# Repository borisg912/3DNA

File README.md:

# 3DNA - Interactive DNA Learning Model

**3DNA** is an educational 3D-printed DNA model that combines physical structure with interactive electronics to help students understand DNA base pairing through hands-on learning.

**Website**: [Project showcase and app downloads](Website)

## 🧬 Project Overview

This project creates a flat cylindrical DNA model with:
- **Magnetic DNA bases** with color-coded NeoPixel LEDs and unique resistor values for identification
- **Interactive base pairing game** that validates correct DNA base connections
- **Smart home integration** with multiple connectivity options
- **Companion applications** for Android and Windows

## 📦 Components

### Hardware
- **ESP32-C6** microcontroller on custom PCB (3-3.3V logic)
- **13 DNA bases** (12 helix positions + 1 foundation) with NeoPixels and resistors
- **2x CD74HC4067 multiplexers**: one at 3.3V for resistor voltage divider, one at 5V for NeoPixel control
- **SN74AHCT125N** buffer gate for driving 5V signals from ESP32's 3V
- **TEMT6000** ambient light sensor for dynamic brightness control
- **MPU-6500** gyroscope/inclinometer for spatial orientation
- **DFPlayer Mini** for audio feedback
- **BQ25895** power management IC with USB/USB-C quick charging (up to 9V, 25W@3A)
- **MP8715** voltage regulator (5-9V to 5V)
- **4x 18650 Li-ion batteries** (user-replaceable) with per-cell protection: PPTC fuses + AO3401A + DW01 + FS8205A
- **FQP30N06L** MOSFET for fan control
- **BAT54C** Schottky diode
- **NeoPixel strips** for visual effects (5V)
- **Touch button** for user interaction
- **Backboard button** for system functions

### Software
- **ESP-IDF firmware** for ESP32-C6
- **Android application** for mobile control
- **Windows UWP application** for desktop

## 🎯 Features

### Interactive Learning Mode
- **Base Identification**: Each base has a unique resistor value read via voltage divider
- **Color Coding**: NeoPixels light up in base-specific colors (A, T, C, G)
- **Pair Validation**: Check correct base pairing (A-T, C-G) with visual feedback
- **Error Highlighting**: Wrong bases light up in red for easy identification

### Smart Home Mode
- **Multi-protocol connectivity**: Wi-Fi, Bluetooth/BLE, Zigbee, Thread
- **Remote control**: Control NeoPixels via companion apps
- **Motion sensing**: Gyroscope triggers commands on movement
- **Ambient lighting**: Dynamic brightness based on environment

### Power Management
- **Battery operation**: 2-4 cell configuration
- **USB charging**: With power delivery management
- **Sleep modes**: Low-power states for battery conservation
- **Thermal management**: Fan control based on temperature

## 🛠️ Development Status

- **Hardware**: PCB design in KiCad (v4.1 final)
- **Firmware**: ESP-IDF framework with modular components
- **Mobile**: Android app foundation
- **Desktop**: Windows UWP app starter

## 📁 Project Structure

```
3DNA/
├── Embedded/          KiCad PCB files
├── EmbeddedCode/      ESP32-C6 firmware (ESP-IDF)
├── AppAndroid/        Android mobile app
├── AppWindows/        Windows UWP desktop app
├── Website/           Project showcase website
└── Assets/            Graphics and media
```

## 📄 Documentation

- [English README](README.md)
- [Български README](README.BG.md)

## 🤝 Contributing

This is a school project developed for educational purposes. Contributions and feedback are welcome for improving the learning experience and technical implementation.

## 📜 License

This project is licensed under **GNU GPL v3** - see [LICENSE](LICENSE) for details.

---

*Built with passion for education and technology*

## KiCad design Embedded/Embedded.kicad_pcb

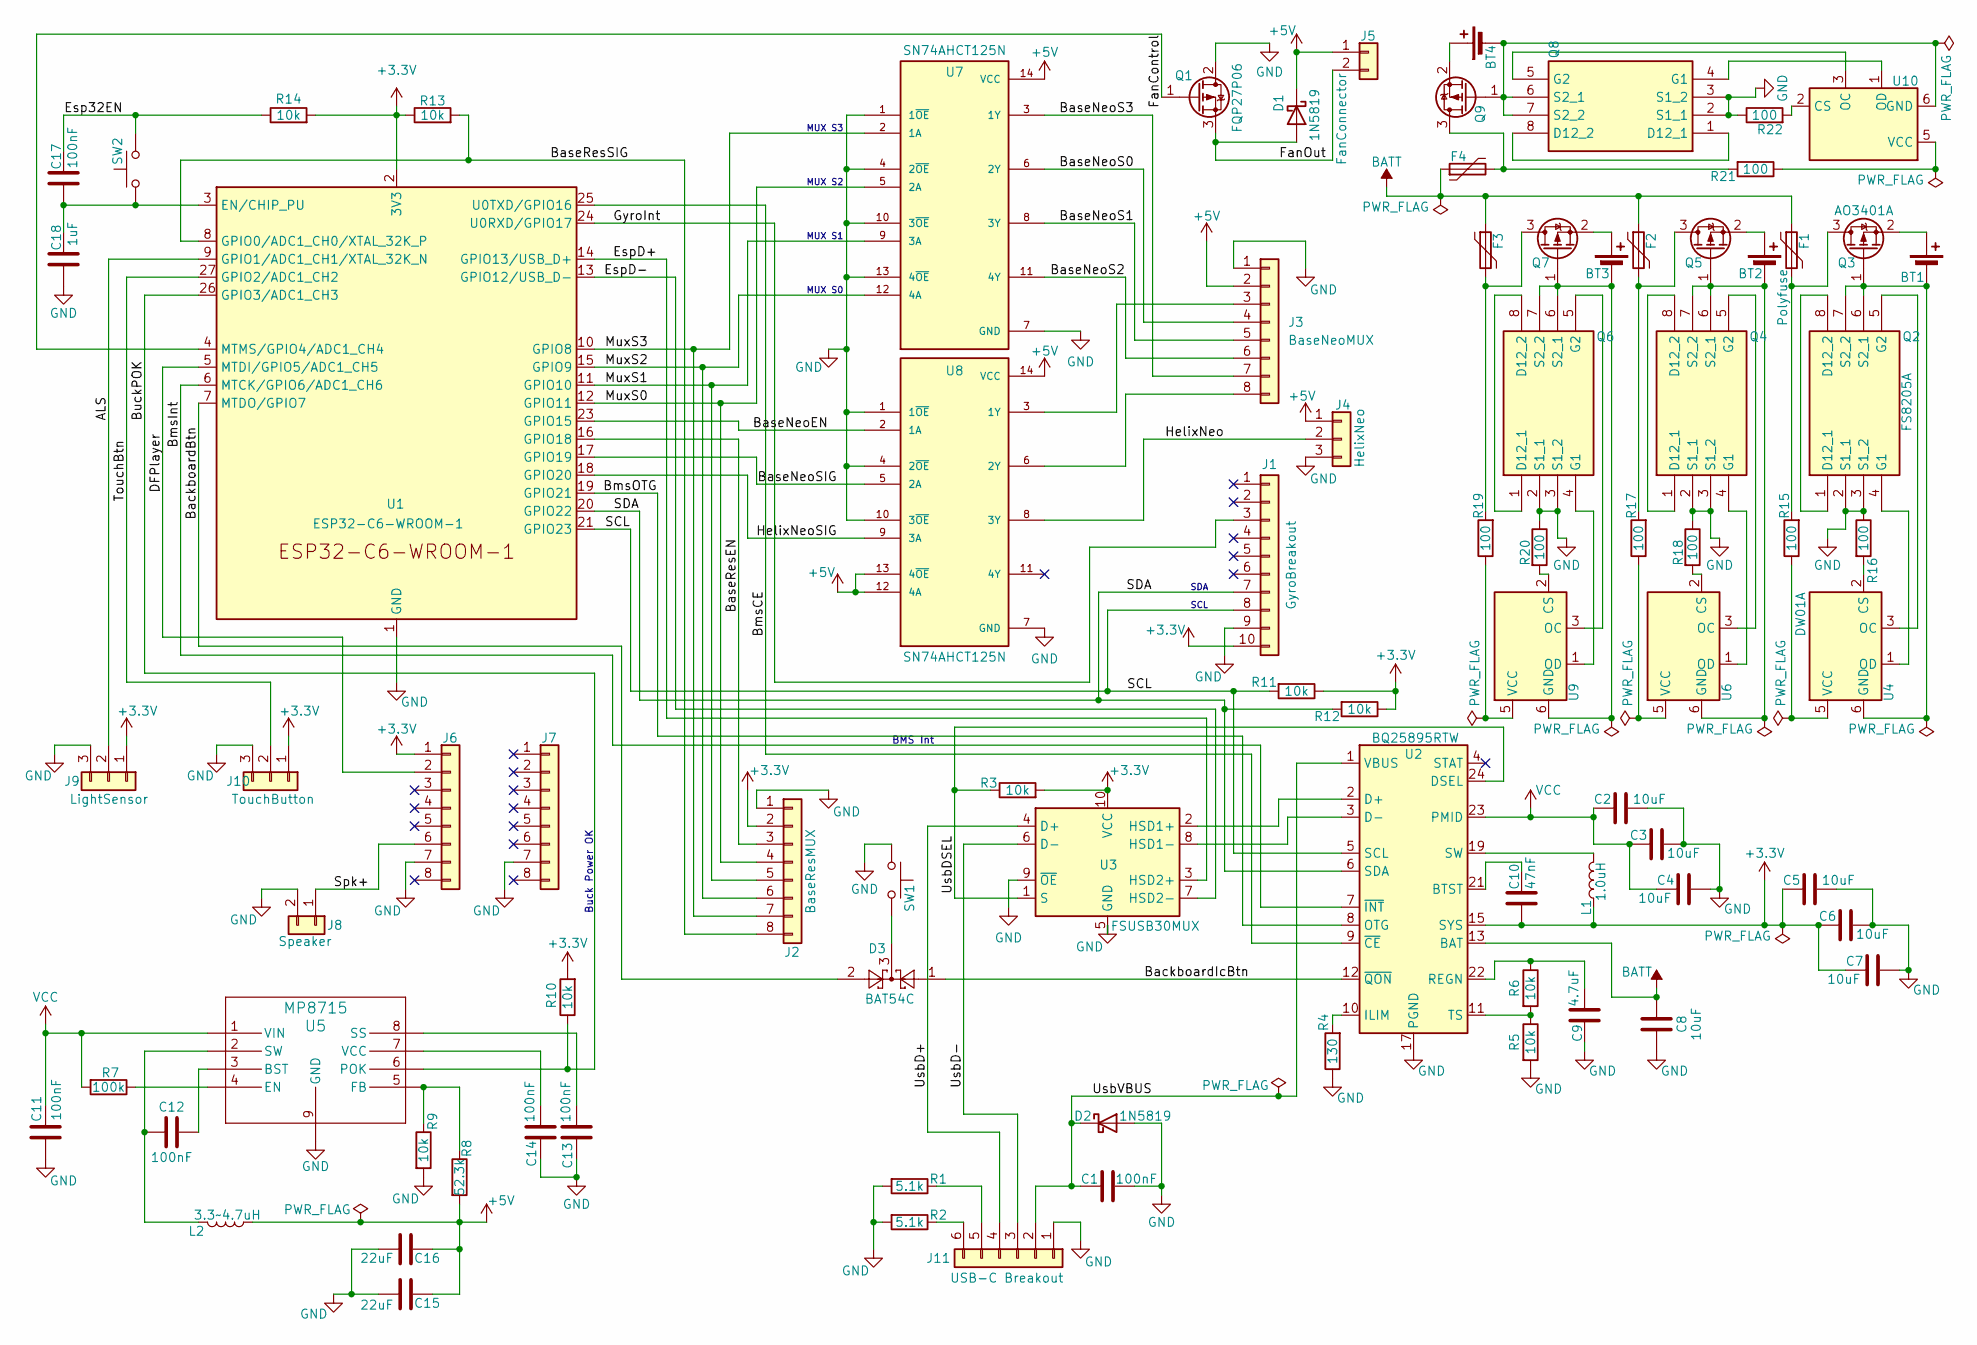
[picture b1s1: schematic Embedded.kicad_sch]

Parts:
BT1, BT2, BT3, BT4: Battery_Cell; JST_PH_B2B-PH-K_1x02_P2.00mm_Vertical
C1, C11, C12, C13, C14, C17: 100nF; C_0402_1005Metric_Pad0.74x0.62mm_HandSolder
C2, C3, C4: 10uF; C_0805_2012Metric_Pad1.18x1.45mm_HandSolder
C5, C6, C7, C8: 10uF; C_0603_1608Metric_Pad1.08x0.95mm_HandSolder
C9: 4.7uF; C_0603_1608Metric_Pad1.08x0.95mm_HandSolder
C10: 47nF; C_0402_1005Metric_Pad0.74x0.62mm_HandSolder
C15, C16: 22uF; C_1206_3216Metric_Pad1.33x1.80mm_HandSolder
C18: 1uF; C_0603_1608Metric_Pad1.08x0.95mm_HandSolder
D1, D2: 1N5819; D_DO-41_SOD81_P10.16mm_Horizontal
D3: BAT54C; SOT-23
F1, F2, F3, F4: Polyfuse; Fuse_1206_3216Metric_Pad1.42x1.75mm_HandSolder
J1: GyroBreakout; PinHeader_1x10_P2.54mm_Vertical
J2: BaseResMUX; PinHeader_1x08_P2.54mm_Vertical
J3: BaseNeoMUX; PinHeader_1x08_P2.54mm_Vertical
J4: HelixNeo; PinHeader_1x03_P2.54mm_Horizontal
J5: FanConnector; PinHeader_1x02_P2.54mm_Horizontal
J6, J7: Conn_01x08; PinHeader_1x08_P2.54mm_Vertical
J8: Speaker; PinHeader_1x02_P2.54mm_Horizontal
J9: LightSensor; PinHeader_1x03_P2.54mm_Horizontal
J10: TouchButton; PinHeader_1x03_P2.54mm_Horizontal
J11: USB-C Breakout; PinHeader_1x06_P2.54mm_Horizontal
L1: 1.0uH; L_Ferrocore_DLG-0403
L2: 3.3~4.7uH; L_Ferrocore_DLG-0403
Q1: FQP27P06; TO-220-3_Horizontal_TabDown
Q2, Q4, Q6, Q8: FS8205A; MSOP-8_3x3mm_P0.65mm; Manufacturer_Part_Number FS8205A
Q3, Q5, Q7, Q9: AO3401A; TSOT-23_HandSoldering
R1, R2: 5.1k; R_Axial_DIN0207_L6.3mm_D2.5mm_P10.16mm_Horizontal
R3, R5, R6, R9, R10, R11, R12, R13, R14: 10k; R_Axial_DIN0207_L6.3mm_D2.5mm_P10.16mm_Horizontal
R4: 130; R_Axial_DIN0207_L6.3mm_D2.5mm_P10.16mm_Horizontal
R7: 100k; R_Axial_DIN0207_L6.3mm_D2.5mm_P10.16mm_Horizontal
R8: 52.3k; R_Axial_DIN0207_L6.3mm_D2.5mm_P10.16mm_Horizontal
R15, R16, R17, R18, R19, R20, R21, R22: 100; R_Axial_DIN0207_L6.3mm_D2.5mm_P10.16mm_Horizontal
SW1, SW2: BackboardSw; SW_PUSH_6mm_H5mm
U1: ESP32-C6-WROOM-1
U2: BQ25895RTW; Texas_RTW_WQFN-24-1EP_4x4mm_P0.5mm_EP2.7x2.7mm_ThermalVias
U3: FSUSB30MUX; MSOP-10_3x3mm_P0.5mm
U4, U6, U9, U10: DW01A; SOT-23-6
U5: MP8715; SOIC8_MP8001A_MNP
U7, U8: SN74AHCT125N; DIP794W45P254L1930H508Q14; PARTREV Q

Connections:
+3.3V: C5.1, C6.2, C7.1, C10.1, J1.10, J2.2, J6.1, J9.1, J10.1, L1.1, R3.2, R10.2, R11.1, R12.1, R13.1, R14.2, U1.2 (3V3), U2.15 (SYS), U2.16 (SYS), U3.10 (VCC)
+5V: C15.1, C16.1, D1.1 (K), J3.2, J4.1, J5.1, L2.1, R8.2, U7.14 (VCC), U8.12 (4A), U8.13 (4~OE), U8.14 (VCC)
/ALS: J9.2, U1.9 (GPIO1/ADC1_CH1/XTAL_32K_N)
/BackboardBtn: D3.2, U1.7 (MTDO/GPIO7)
/BackboardIcBtn: D3.1, U2.12 (~QON)
/BaseNeoEN: U1.23 (GPIO15), U8.2 (1A)
/BaseNeoS0: J3.4, U7.6 (2Y)
/BaseNeoS1: J3.5, U7.8 (3Y)
/BaseNeoS2: J3.6, U7.11 (4Y)
/BaseNeoS3: J3.7, U7.3 (1Y)
/BaseNeoSIG: U1.17 (GPIO19), U8.5 (2A)
/BaseResEN: J2.3, U1.16 (GPIO18)
/BaseResSIG: J2.8, R13.2, U1.8 (GPIO0/ADC1_CH0/XTAL_32K_P)
/BmsCE: U1.25 (U0TXD/GPIO16), U2.9 (~CE)
/BmsInt: U1.6 (MTCK/GPIO6/ADC1_CH6), U2.7 (~INT)
/BmsOTG: U1.19 (GPIO21), U2.8 (OTG)
/BuckPOK: R10.1, U1.26 (GPIO3/ADC1_CH3), U5.6 (POK)
/DFPlayer: J6.2, U1.5 (MTDI/GPIO5/ADC1_CH5)
/Esp32EN: C17.2, R14.1, SW2.2
/EspD+: U1.14 (GPIO13/USB_D+), U3.3 (HSD2+)
/EspD-: U1.13 (GPIO12/USB_D-), U3.7 (HSD2-)
/FanControl: Q1.1 (G), U1.4 (MTMS/GPIO4/ADC1_CH4)
/FanOut: D1.2 (A), J5.2, Q1.3 (S)
/GyroInt: J1.3, U1.24 (U0RXD/GPIO17)
/HelixNeo: J4.2, U8.8 (3Y)
/HelixNeoSIG: U1.18 (GPIO20), U8.9 (3A)
/MuxS0: J2.4, U1.12 (GPIO11), U7.5 (2A)
/MuxS1: J2.5, U1.11 (GPIO10), U7.9 (3A)
/MuxS2: J2.6, U1.15 (GPIO9), U7.12 (4A)
/MuxS3: J2.7, U1.10 (GPIO8), U7.2 (1A)
/SCL: J1.8, R11.2, U1.21 (GPIO23), U2.5 (SCL)
/SDA: J1.7, R12.2, U1.20 (GPIO22), U2.6 (SDA)
/Spk+: J6.6, J8.1
/TouchBtn: J10.2, U1.27 (GPIO2/ADC1_CH2)
/UsbD+: J11.4, U3.4 (D+)
/UsbD-: J11.3, U3.6 (D-)
/UsbDSEL: R3.1, U2.24 (DSEL), U3.1 (S)
/UsbVBUS: C1.1, D2.1 (K), J11.2, U2.1 (VBUS)
BATT: C8.2, F1.1, F2.1, F3.1, F4.1, U2.13 (BAT), U2.14 (BAT)
GND: C1.2, C2.2, C3.1, C4.2, C5.2, C6.1, C7.2, C8.1, C9.1, C11.1, C13.2, C14.2, C15.2, C16.2, C18.1, D2.2 (A), J1.9, J2.1, J3.1, J4.3, J6.7, J7.7 (Pin_7_7), J8.2, J9.3, J10.3, J11.1, Q1.2 (D), Q2.2 (S1_1), Q2.3 (S1_2), Q4.2 (S1_1), Q4.3 (S1_2), Q6.2 (S1_1), Q6.3 (S1_2), Q8.2 (S1_1), Q8.3 (S1_2), R1.2, R2.2, R4.1, R5.2, R9.2, R16.1, R18.1, R20.1, R22.1, SW1.1, U1.1 (GND), U1.28 (GND), U1.29 (GND), U2.17 (PGND), U2.18 (PGND), U2.25 (PGND), U3.5 (GND), U3.9 (~OE), U5.9 (GND), U7.1 (1~OE), U7.4 (2~OE), U7.7 (GND), U7.10 (3~OE), U7.13 (4~OE), U8.1 (1~OE), U8.4 (2~OE), U8.7 (GND), U8.10 (3~OE)
unnamed: BT1.1 (+), Q3.2 (S)
unnamed: BT1.2 (-), Q2.6 (S2_1), Q2.7 (S2_2), Q3.1 (G), U4.6 (GND)
unnamed: BT2.1 (+), Q5.2 (S)
unnamed: BT2.2 (-), Q4.6 (S2_1), Q4.7 (S2_2), Q5.1 (G), U6.6 (GND)
unnamed: BT3.1 (+), Q7.2 (S)
unnamed: BT3.2 (-), Q6.6 (S2_1), Q6.7 (S2_2), Q7.1 (G), U9.6 (GND)
unnamed: BT4.1 (+), Q9.2 (S)
unnamed: BT4.2 (-), Q8.6 (S2_1), Q8.7 (S2_2), Q9.1 (G), U10.6 (GND)
unnamed: D3.3, SW1.2
unnamed: J3.3, U8.3 (1Y)
unnamed: J3.8, U8.6 (2Y)
unnamed: J11.5, R1.1
unnamed: J11.6, R2.1
unnamed: L1.2, U2.19 (SW), U2.20 (SW)
unnamed: Q2.1 (D12_1), Q2.8 (D12_2)
unnamed: Q2.4 (G1), U4.1 (OD)
unnamed: Q2.5 (G2), U4.3 (OC)
unnamed: F1.2, Q3.3 (D), R15.2
unnamed: Q4.1 (D12_1), Q4.8 (D12_2)
unnamed: Q4.4 (G1), U6.1 (OD)
unnamed: Q4.5 (G2), U6.3 (OC)
unnamed: F2.2, Q5.3 (D), R17.2
unnamed: Q6.1 (D12_1), Q6.8 (D12_2)
unnamed: Q6.4 (G1), U9.1 (OD)
unnamed: Q6.5 (G2), U9.3 (OC)
unnamed: F3.2, Q7.3 (D), R19.2
unnamed: Q8.1 (D12_1), Q8.8 (D12_2)
unnamed: Q8.4 (G1), U10.1 (OD)
unnamed: Q8.5 (G2), U10.3 (OC)
unnamed: F4.2, Q9.3 (D), R21.2
unnamed: C17.1, C18.2, SW2.1, U1.3 (EN/CHIP_PU)
unnamed: C10.2, U2.21 (BTST)
unnamed: U2.2 (D+), U3.2 (HSD1+)
unnamed: U2.3 (D-), U3.8 (HSD1-)
unnamed: R4.2, U2.10 (ILIM)
unnamed: C9.2, R6.1, U2.22 (REGN)
unnamed: R5.1, R6.2, U2.11 (TS)
unnamed: R16.2, U4.2 (CS)
unnamed: R15.1, U4.5 (VCC)
unnamed: C12.2, U5.3 (BST)
unnamed: R7.1, U5.4 (EN)
unnamed: R8.1, R9.1, U5.5 (FB)
unnamed: C13.1, U5.8 (SS)
unnamed: C12.1, L2.2, U5.2 (SW)
unnamed: C14.1, U5.7 (VCC)
unnamed: R18.2, U6.2 (CS)
unnamed: R17.1, U6.5 (VCC)
unnamed: R20.2, U9.2 (CS)
unnamed: R19.1, U9.5 (VCC)
unnamed: R22.2, U10.2 (CS)
unnamed: R21.1, U10.5 (VCC)
VCC: C2.1, C3.2, C4.1, C11.2, R7.2, U2.23 (PMID), U5.1 (VIN)

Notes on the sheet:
SCL
SDA
MUX S3
MUX S2
BMS Int
Buck Power OK
MUX S1
MUX S0

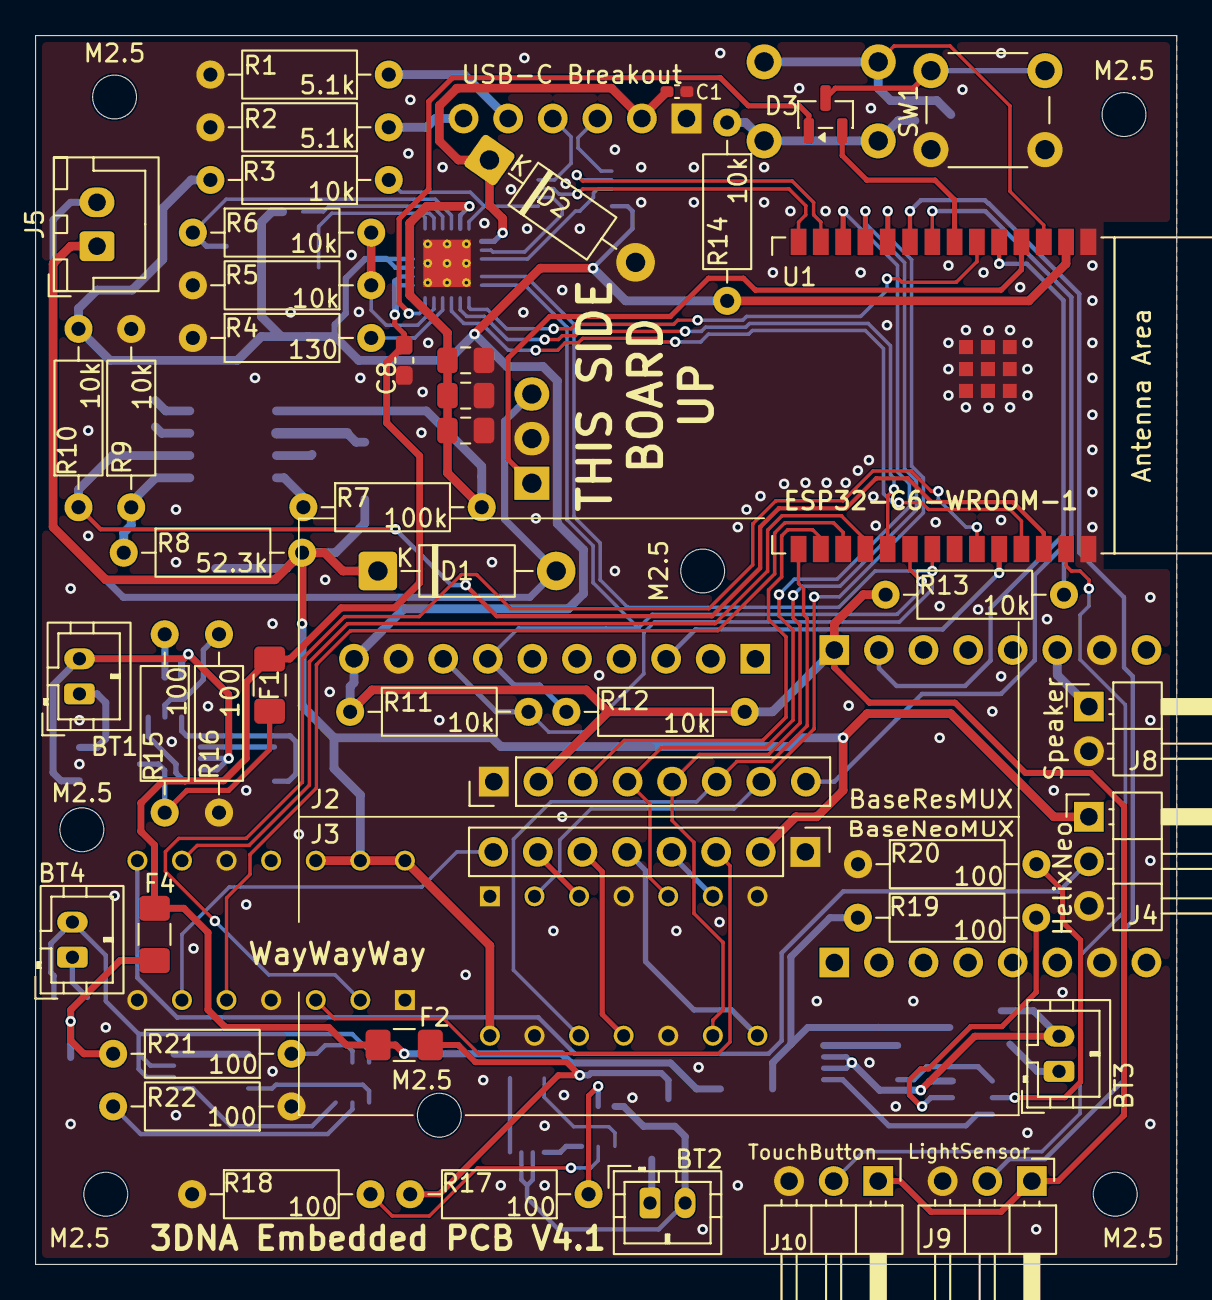
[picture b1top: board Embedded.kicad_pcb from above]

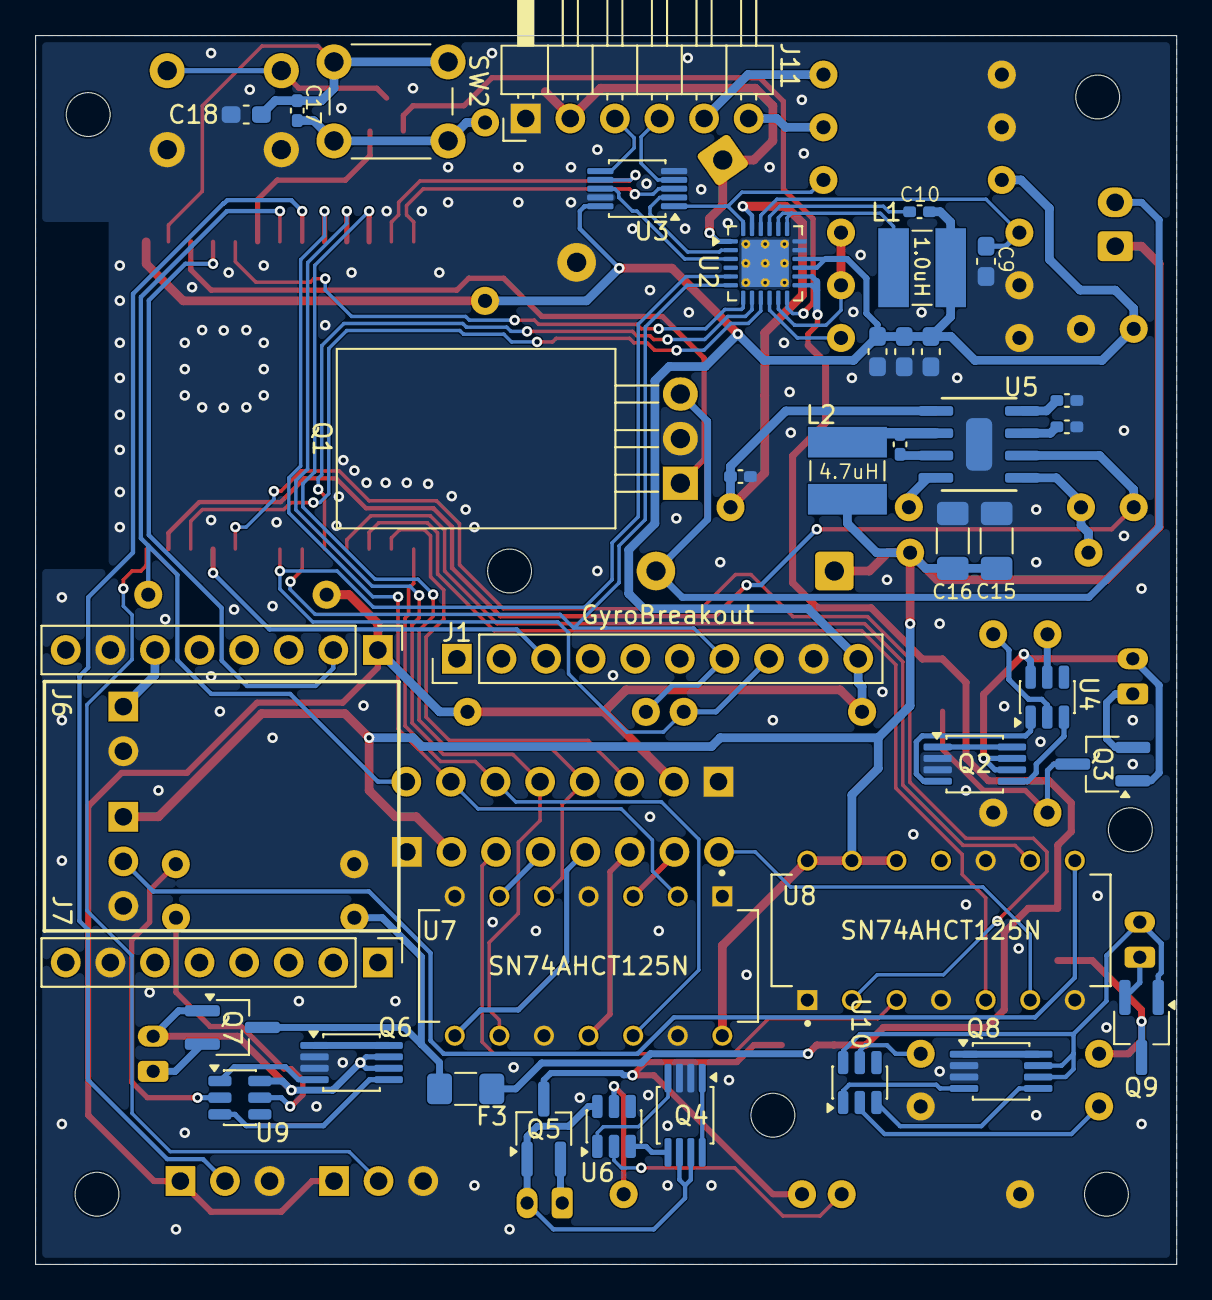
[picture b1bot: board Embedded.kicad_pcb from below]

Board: 2 copper layers, 65.0 x 70.0 mm, 92 parts (39 on the bottom side), 92 nets.

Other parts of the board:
M2.5, M2.5#2, M2.5#3, M2.5#4, M2.5#5, M2.5#6, M2.5#7: MountingHole_2.5mm

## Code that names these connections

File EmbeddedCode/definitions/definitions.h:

#pragma once

#include "driver/gpio.h"
#include "esp_adc/adc_oneshot.h"

// General
#define DnaBaseCount 13     /* 12 helix slots + 1 foundation slot */

// I2C bus
#define I2cSda  22
#define I2cScl  23
#define I2cFreq 100000

// BQ25895
#define BmsInt    6
#define BmsOtg    21
#define BmsCe     16
#define BuckPwrOK 3

// Base Multiplexers (address bits shared by both MUXes)
#define MuxS0          11
#define MuxS1          10
#define MuxS2          9
#define MuxS3          8
#define MuxResEn       18
#define MuxResOut      0
#define MuxResAdcChan  ADC_CHANNEL_0   /* ADC1_CH0 -> GPIO0 */
#define MuxNeoPixelEn  15
#define MuxNeoPixelOut 19

// Sensors
#define LightSensor  1
#define LightAdcChan ADC_CHANNEL_1   /* ADC1_CH1 -> GPIO1 */
#define GyroInt      17

// Helix NeoPixels
#define HelixNeoPixelOut   20
#define HelixNeoPixelCount 40

// Inputs/Outputs
#define TouchButton     2
#define BackboardButton 7
#define AudioPlayerTx   5

// Other
#define FanControl 4
